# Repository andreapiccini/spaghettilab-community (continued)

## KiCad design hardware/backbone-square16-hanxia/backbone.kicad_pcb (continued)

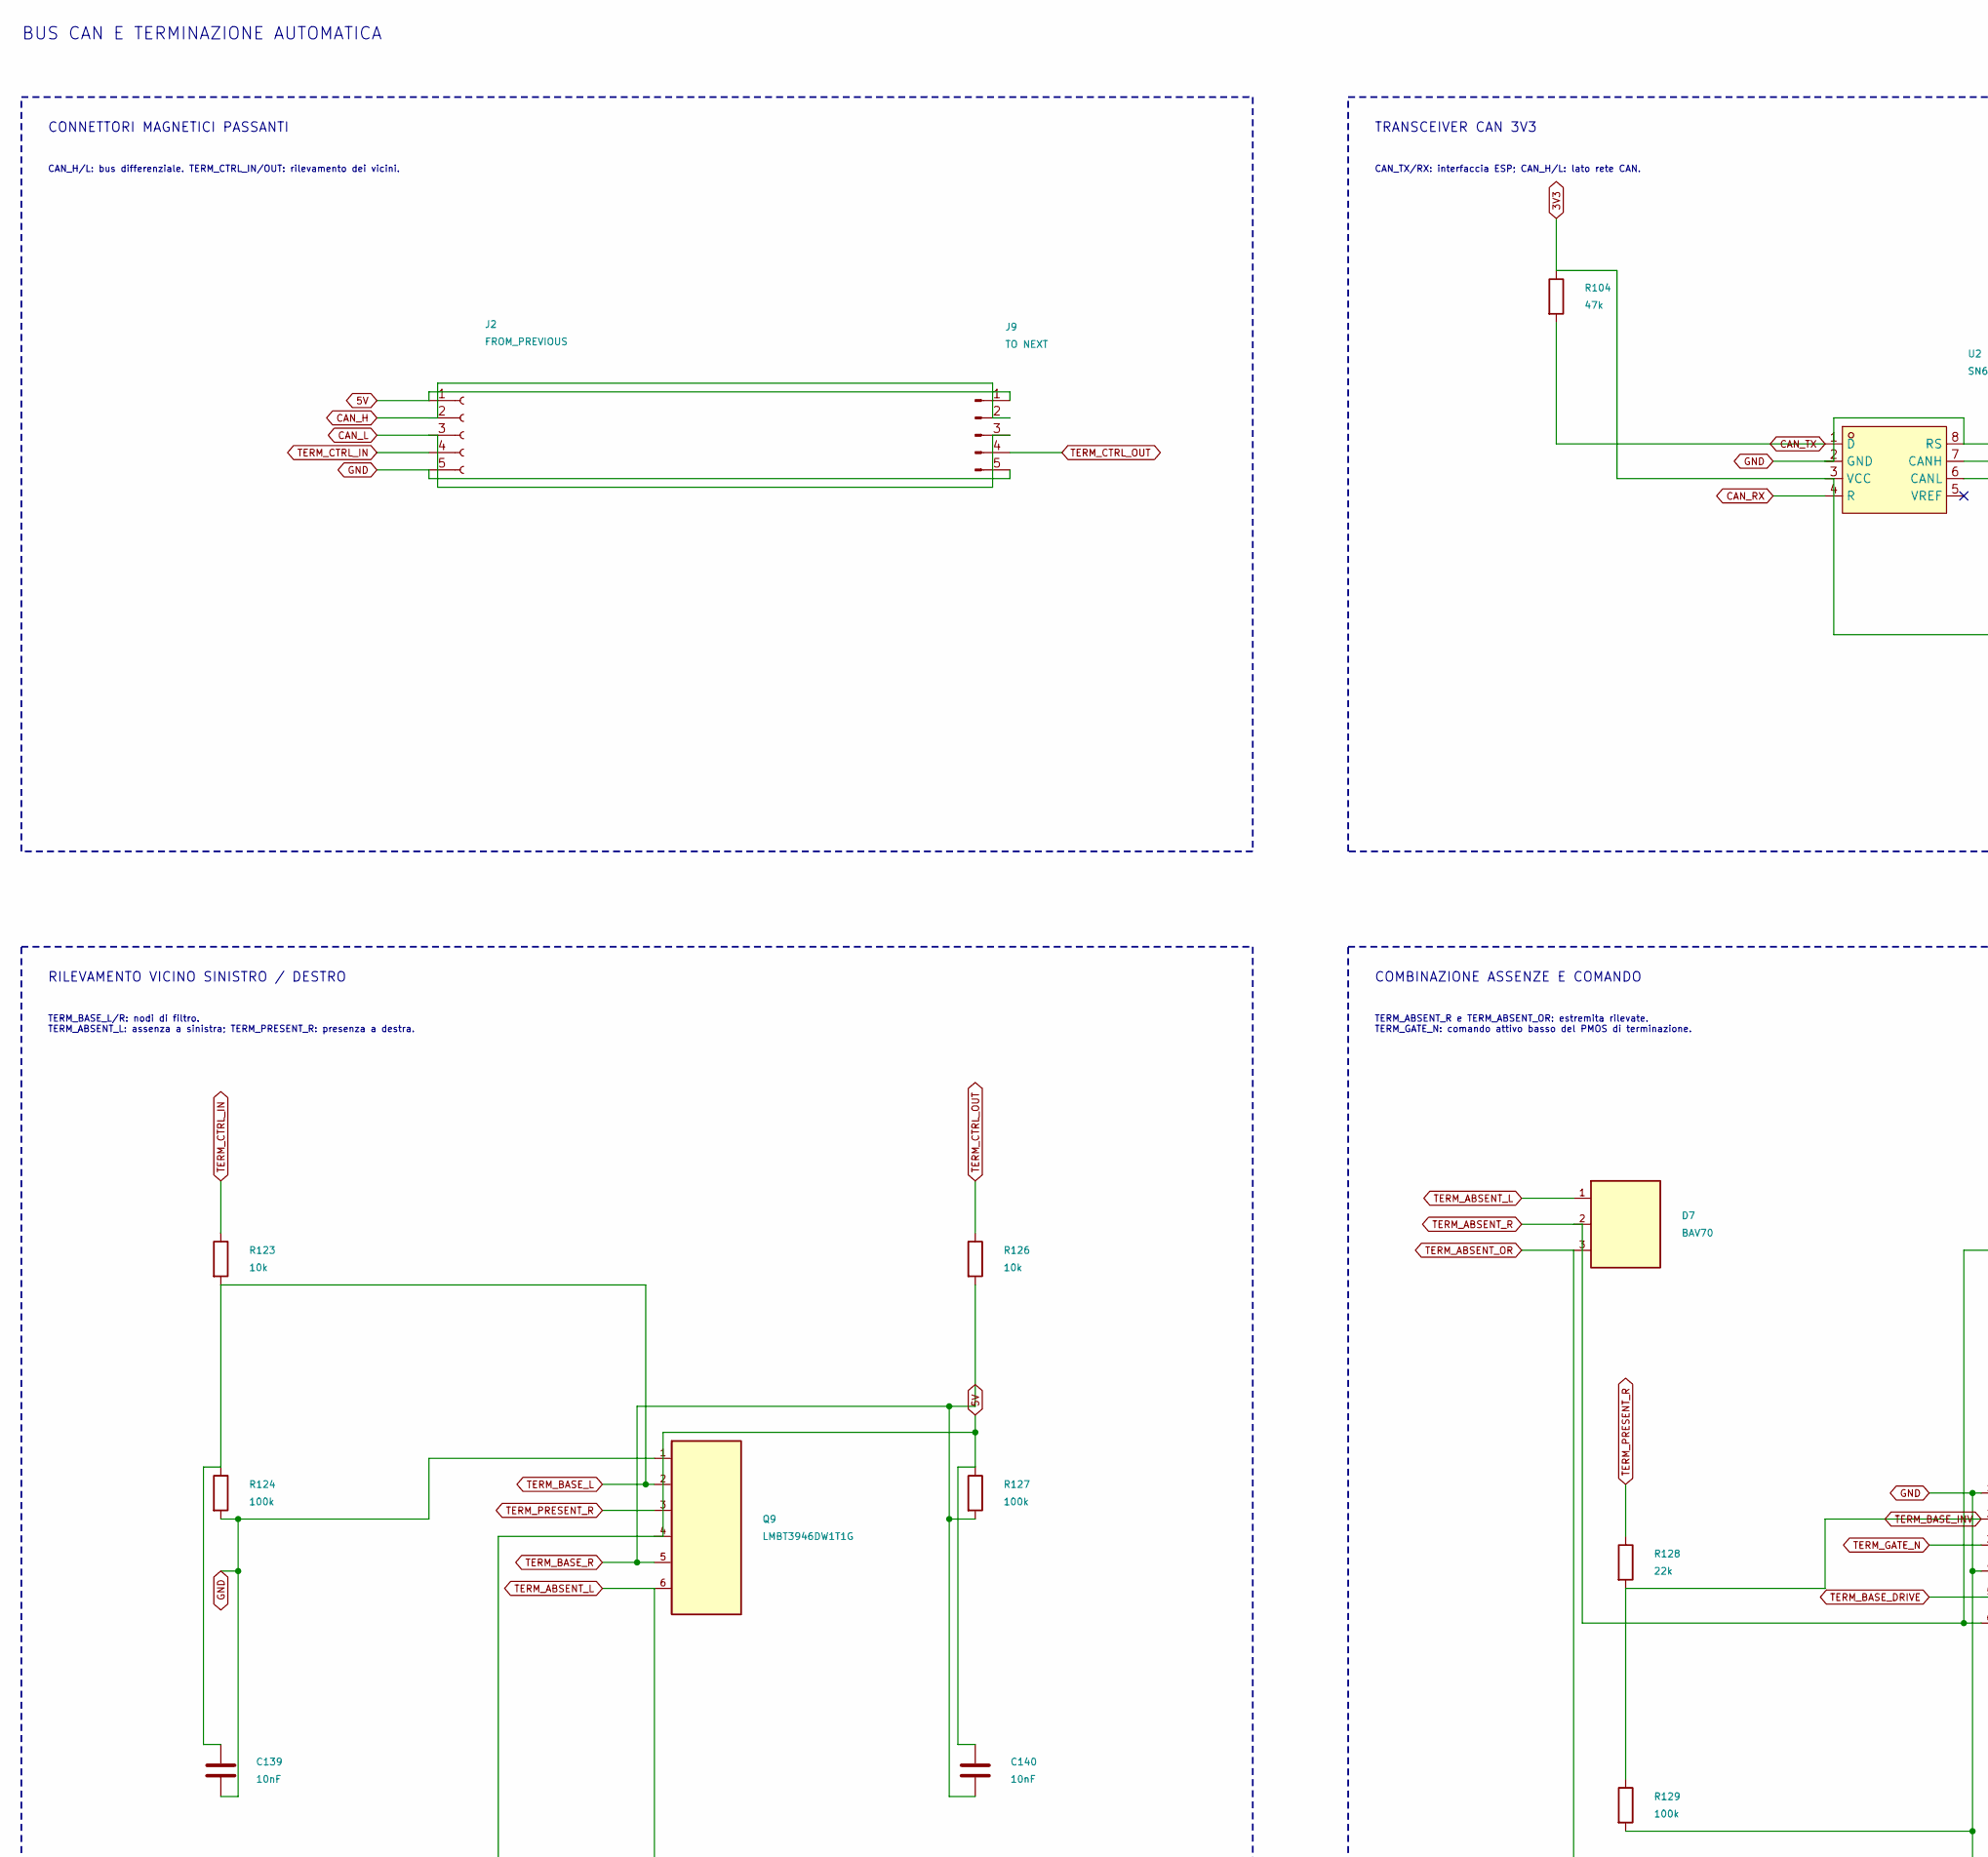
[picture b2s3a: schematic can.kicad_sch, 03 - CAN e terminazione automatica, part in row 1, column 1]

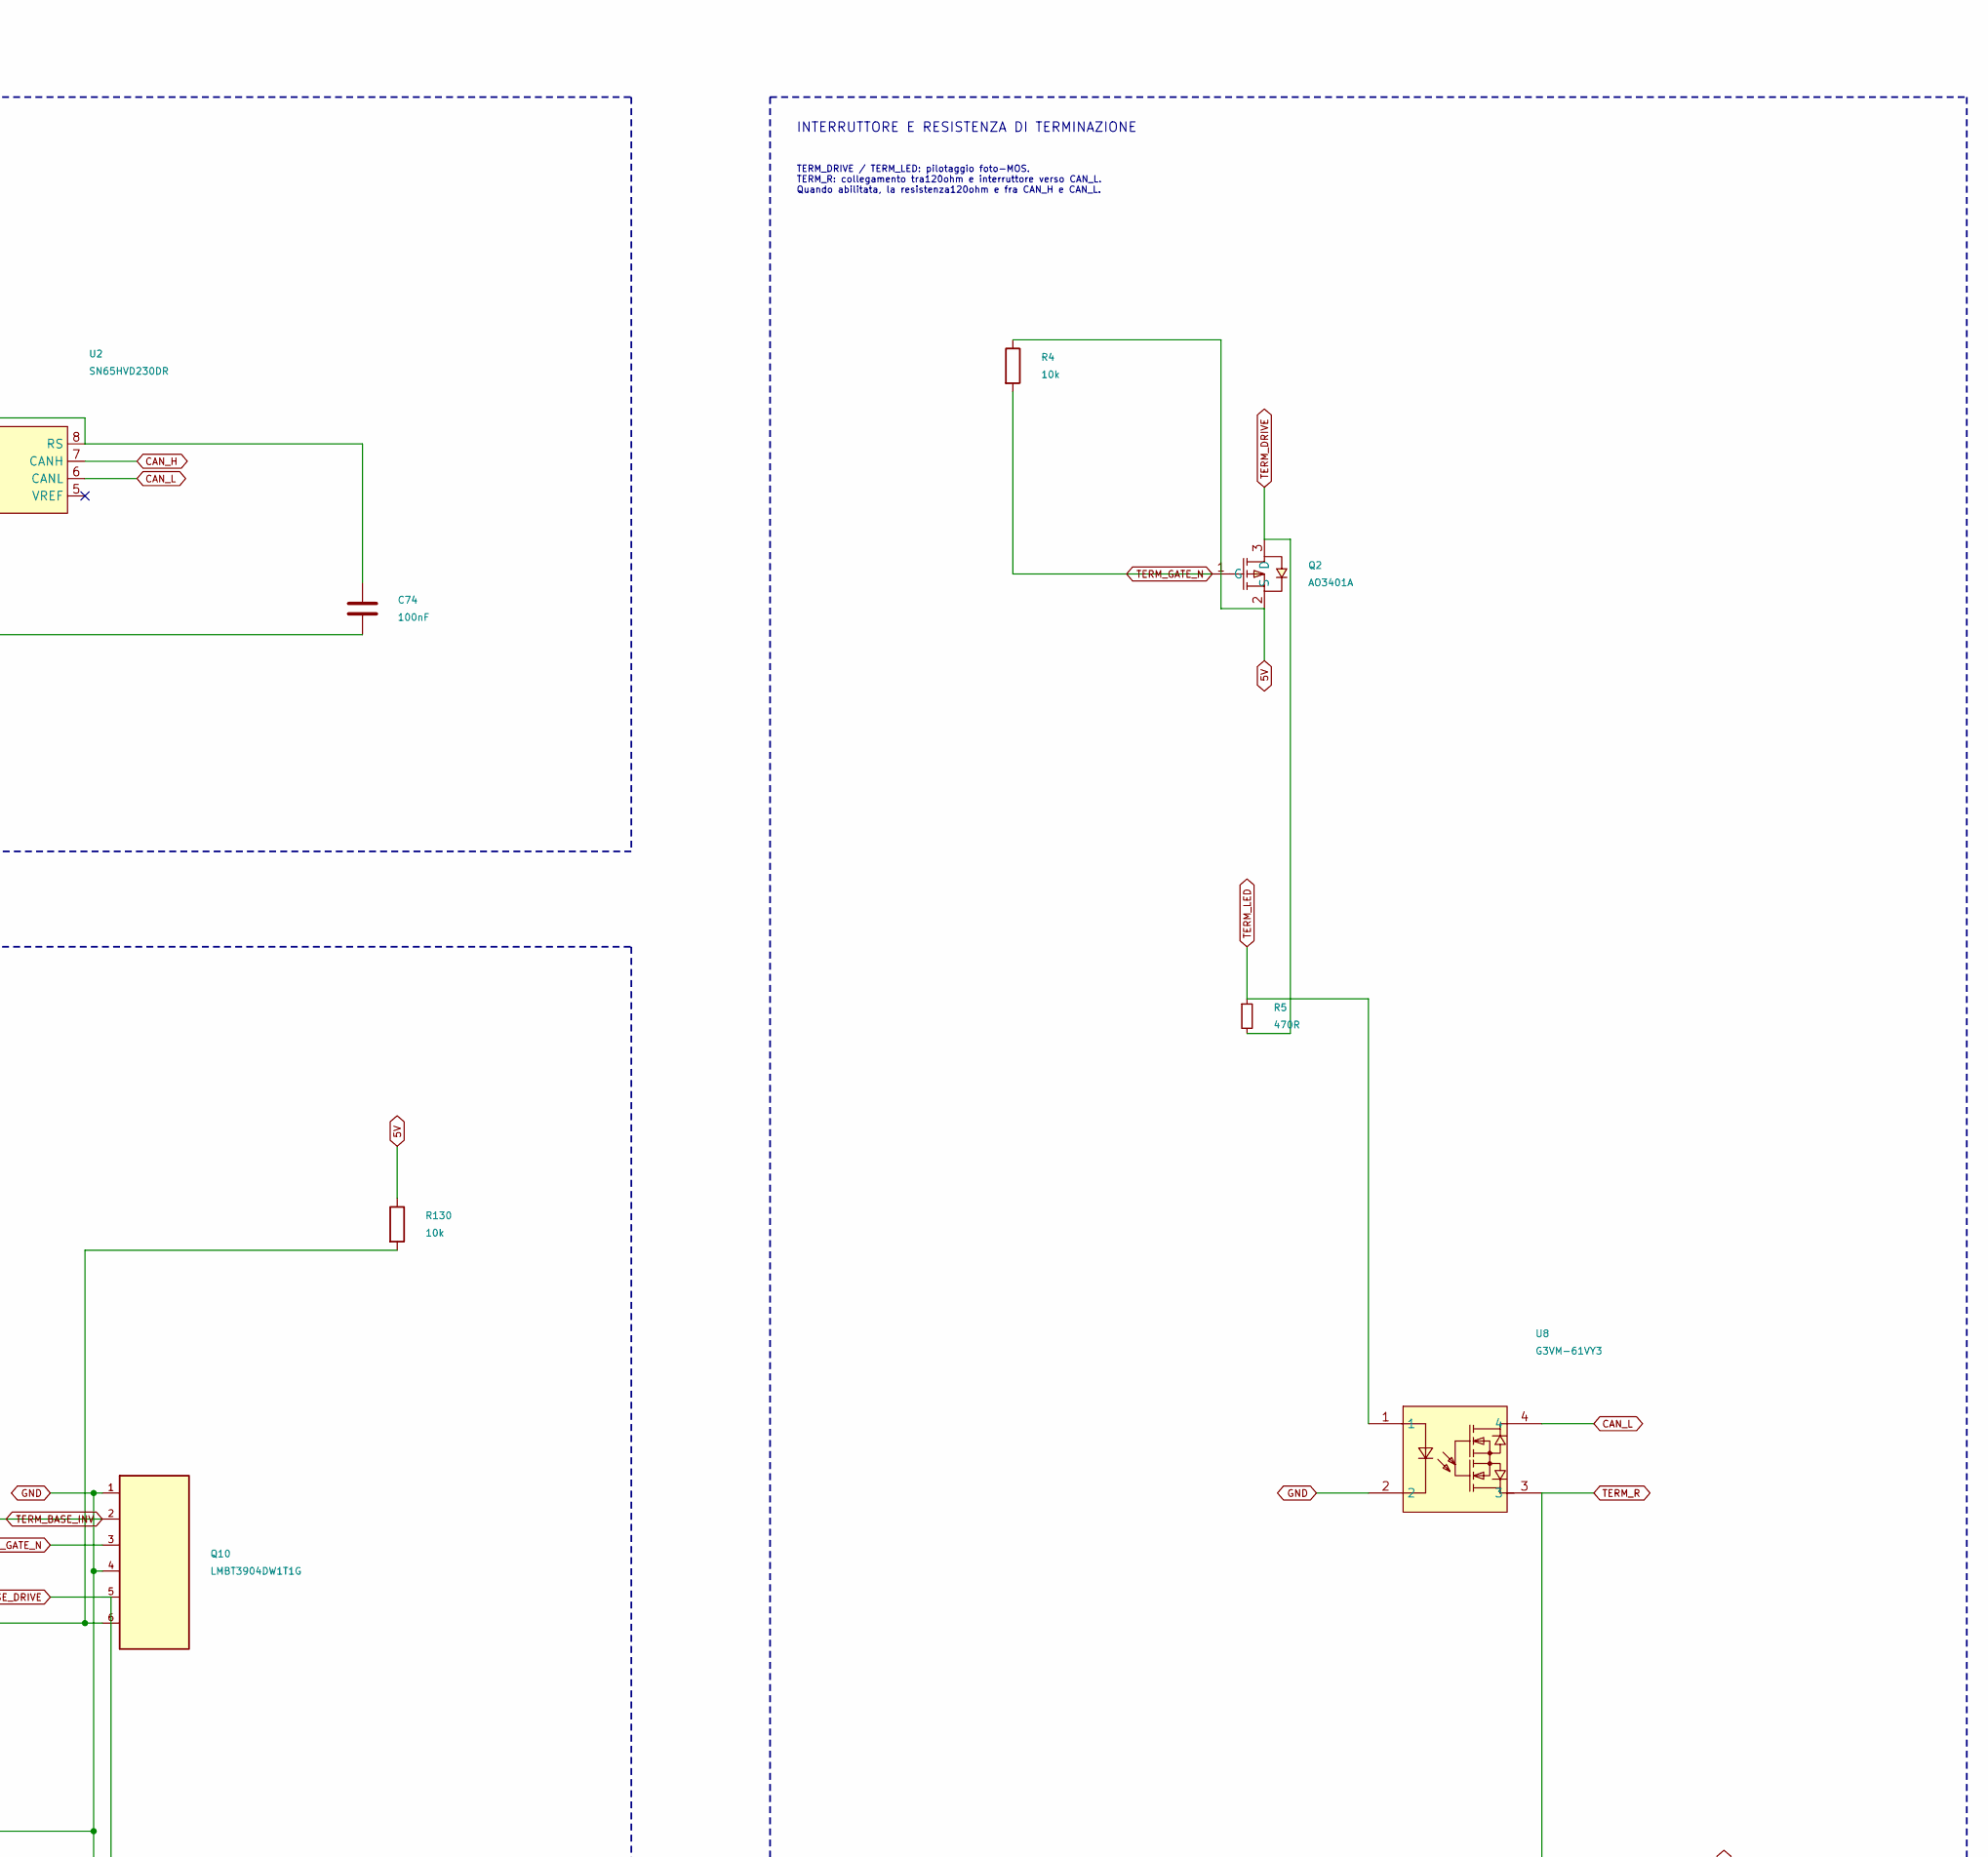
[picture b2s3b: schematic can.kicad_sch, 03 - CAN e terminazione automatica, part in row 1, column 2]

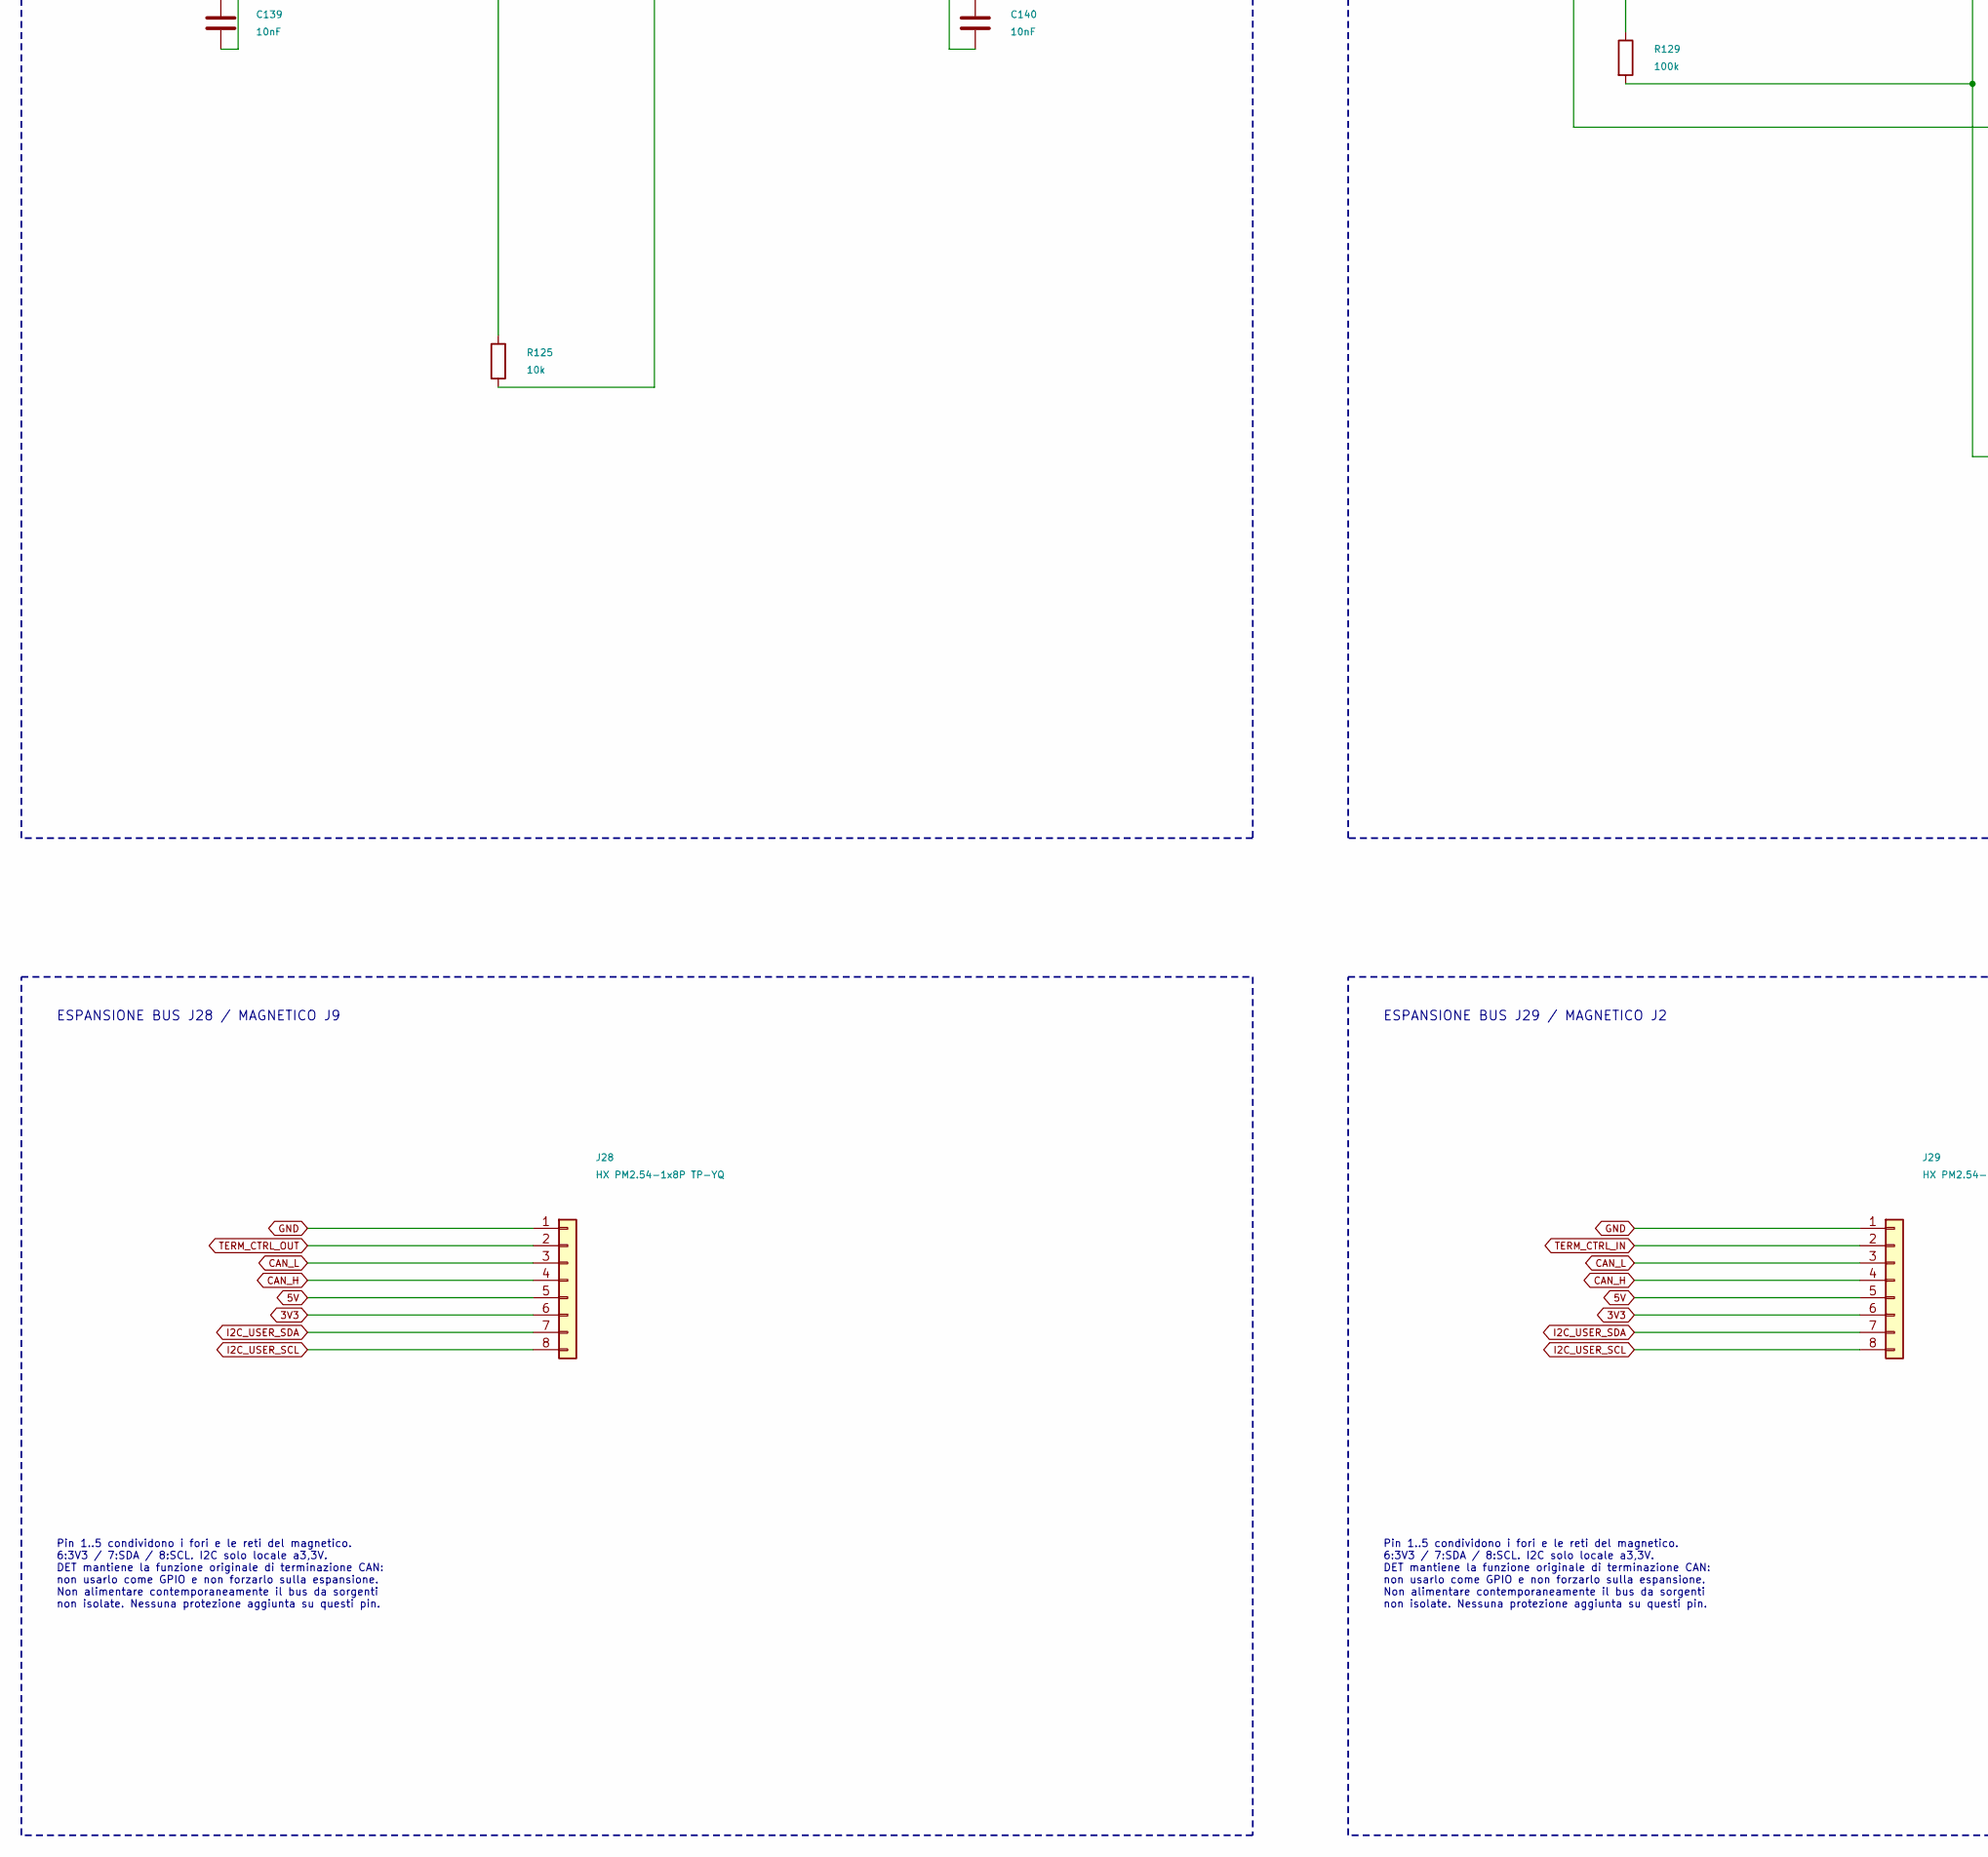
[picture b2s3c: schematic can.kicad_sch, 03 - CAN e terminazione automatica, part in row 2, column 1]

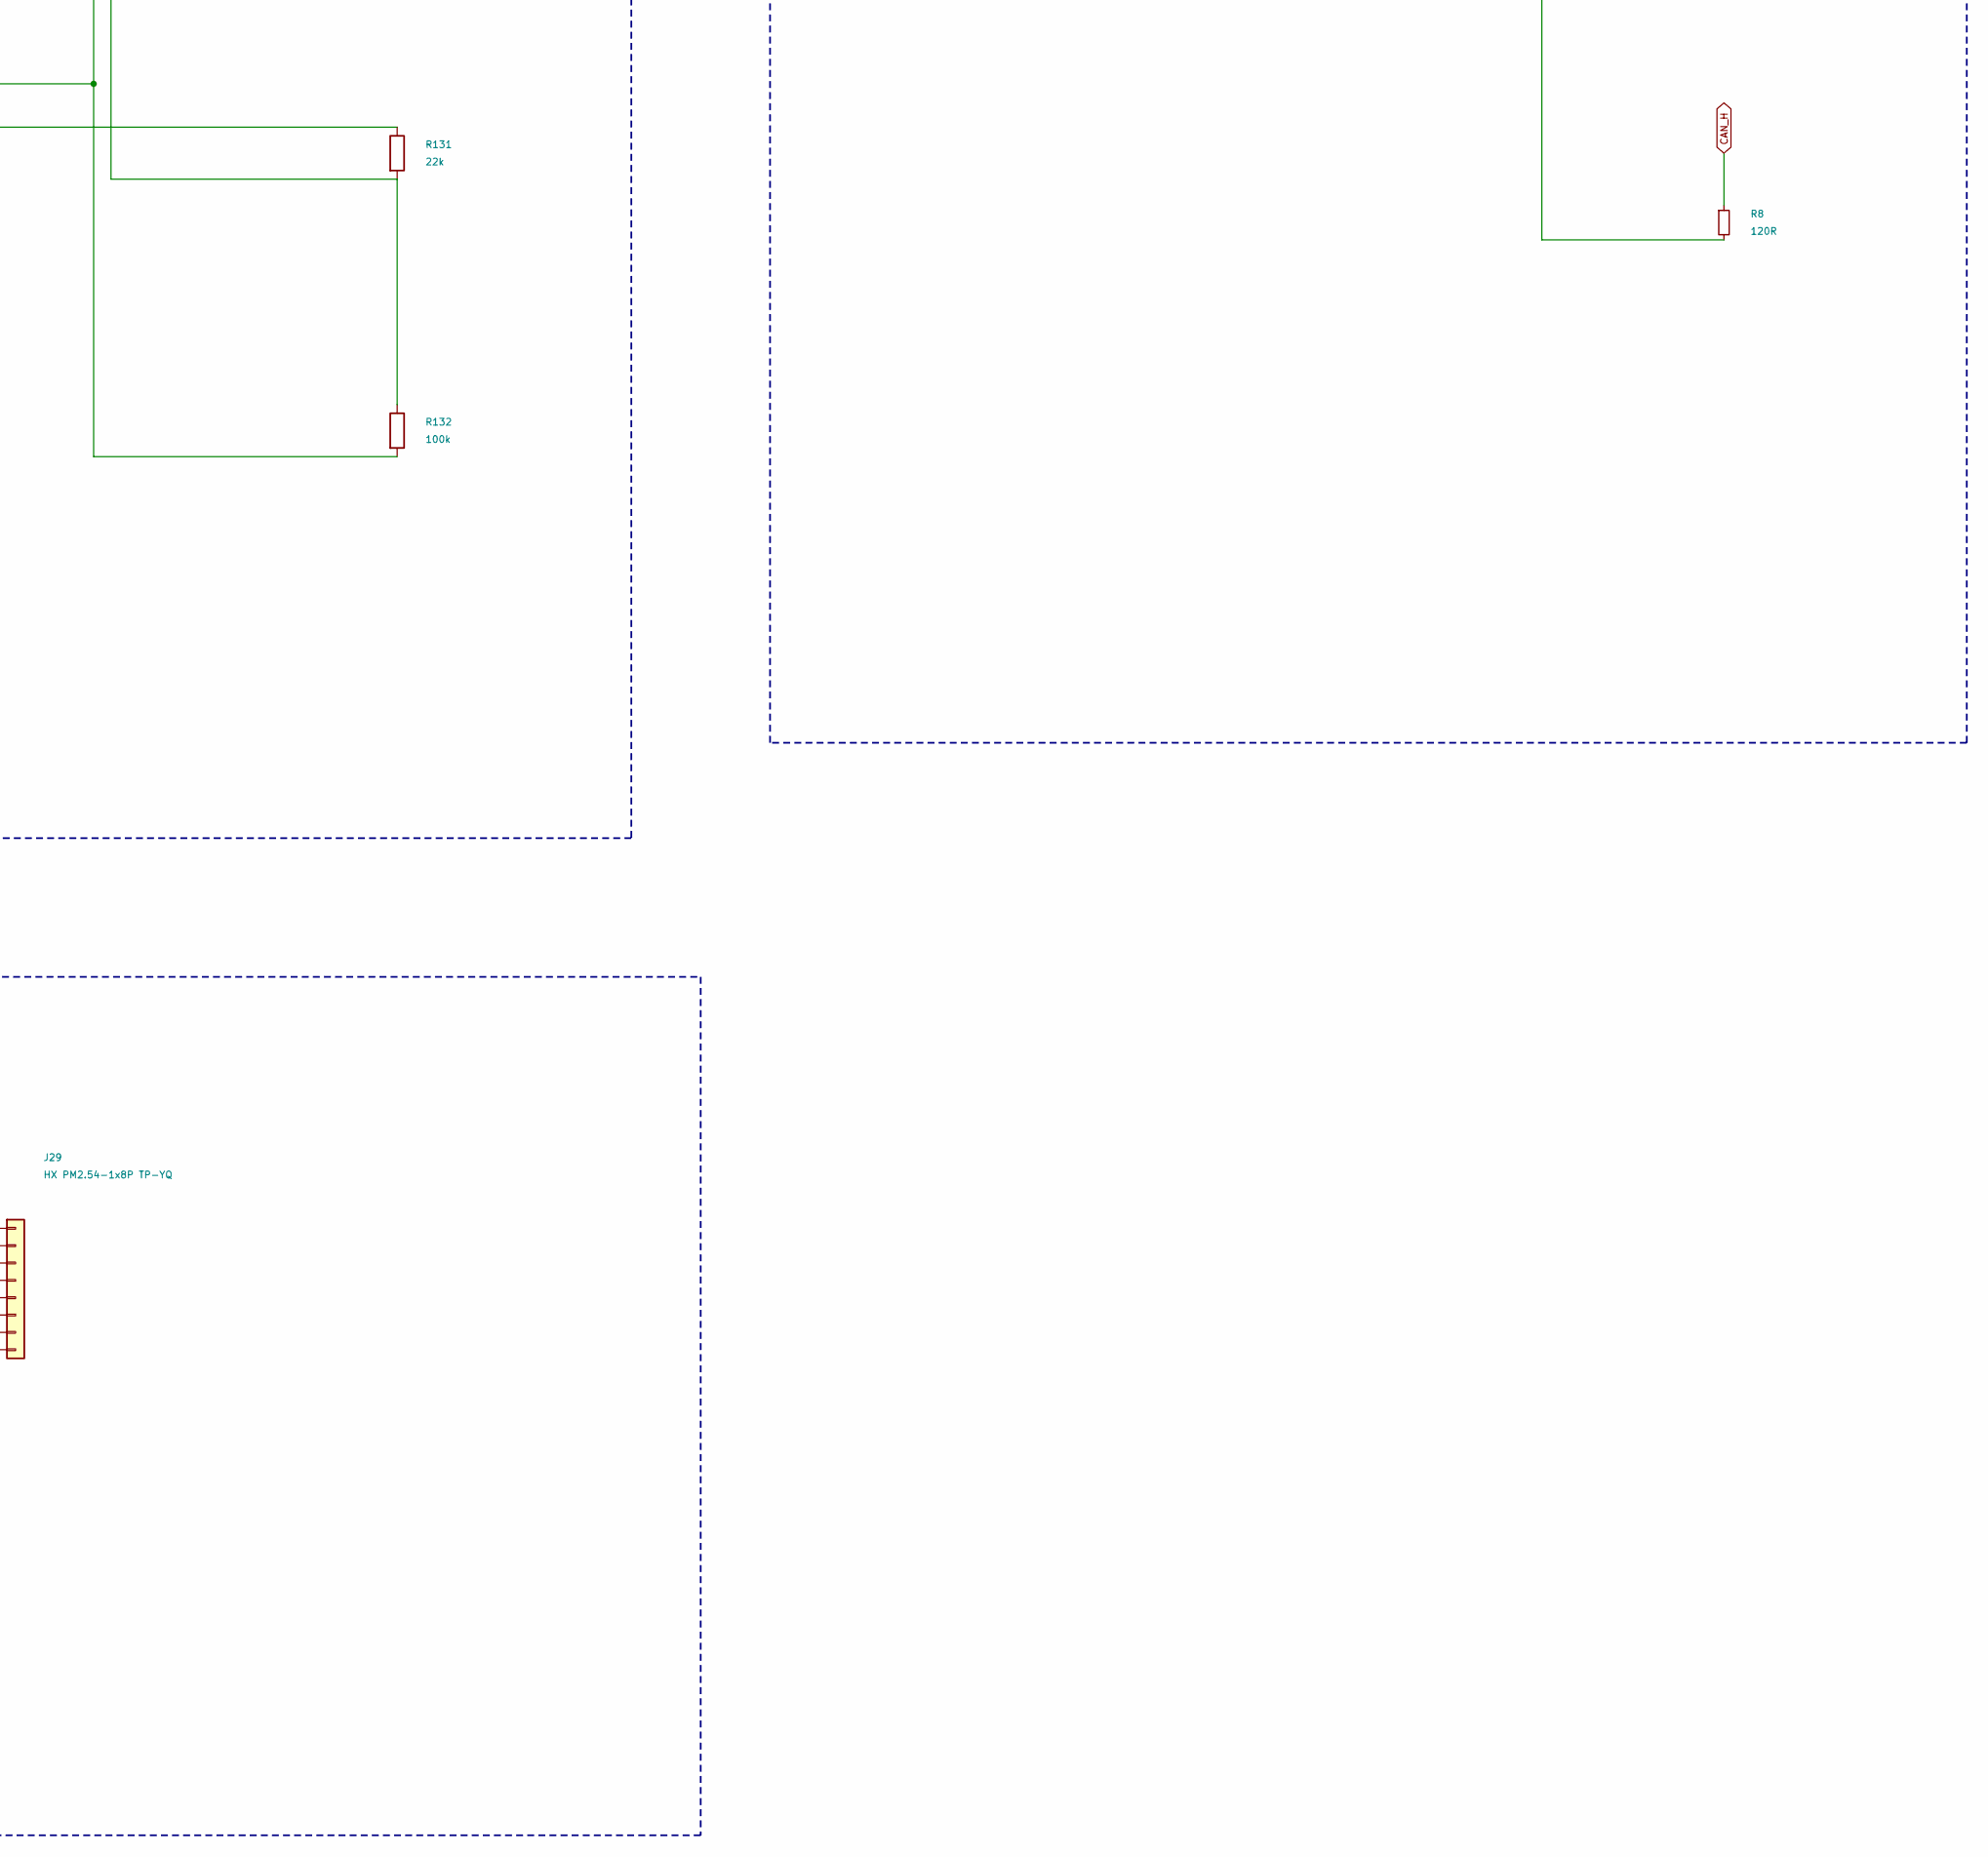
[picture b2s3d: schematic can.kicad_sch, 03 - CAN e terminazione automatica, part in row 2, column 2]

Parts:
C74: 100nF; C_0603_1608Metric
C139, C140: 10nF; C_0603_1608Metric; MPN CL10B103KB8NNNC; LCSC C1589
D7: BAV70; SOT-23; MPN BAV70; LCSC C68978
J2: FROM_PREVIOUS; Magnetic_J2_PTH_Module
J9: TO NEXT; Magnetic_J9_PTH_Module
J28, J29: HX PM2.54-1x8P TP-YQ; Hanxia_C42380985_1x08_MagneticSharedHoles; MPN HX PM2.54-1x8P TP-YQ; LCSC Part C42380985
Q2: AO3401A; SOT-23_L2.9-W1.3-P1.90-LS2.4-BR; MPN AO3401A; LCSC Part C15127
Q9: LMBT3946DW1T1G; SOT-363_SC-70-6; MPN LMBT3946DW1T1G; LCSC C136169
Q10: LMBT3904DW1T1G; SOT-363_SC-70-6; MPN LMBT3904DW1T1G; LCSC C131781
R4: 10k; R_0603_1608Metric
R5: 470R; R0603; MPN 0603WAF4700T5E; LCSC Part Name C23179
R8: 120R; R0603; MPN 0603WAF1200T5E; LCSC Part Name C2906988
R104: 47k; R_0603_1608Metric; MPN 0603WAF4702T5E; LCSC C25819
R123, R125, R126, R130: 10k; R_0603_1608Metric; MPN 0603WAF1002T5E; LCSC C25804
R124, R127, R129, R132: 100k; R_0603_1608Metric; MPN 0603WAF1003T5E; LCSC C25803
R128, R131: 22k; R_0603_1608Metric; MPN 0603WAF2202T5E; LCSC C31850
U2: SN65HVD230DR; SOIC-8_L4.9-W3.9-P1.27-LS6.0-BL; MPN SN65HVD230DR; LCSC Part C12084
U8: G3VM-61VY3; SMD-4_L4.6-W3.7-P2.54-LS7.0-TL; MPN G3VM-61VY3(TR); LCSC Part C2152318

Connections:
3V3: C74.2, J28.6, J29.6, R104.1, U2.3 (VCC); also elsewhere on the board
5V: C140.1, J2.1, J9.1, J28.5, J29.5, Q2.2 (S), Q9.4 (E), R4.1, R125.1, R127.1, R130.1; also elsewhere on the board
CAN_H: J2.2, J9.2, J28.4, J29.4, R8.1, U2.7 (CANH)
CAN_L: J2.3, J9.3, J28.3, J29.3, U2.6 (CANL), U8.4
CAN_RX: U2.4 (R); also elsewhere on the board
CAN_TX: R104.2, U2.1 (D); also elsewhere on the board
GND: C74.1, C139.2, J2.5, J9.5, J28.1, J29.1, Q9.1 (E), Q10.1 (E), Q10.4 (E), R124.2, R129.2, R132.2, U2.2 (GND), U2.8 (RS), U8.2; also elsewhere on the board
I2C_USER_SCL: J28.8, J29.8; also elsewhere on the board
I2C_USER_SDA: J28.7, J29.7; also elsewhere on the board
TERM_ABSENT_L: D7.1 (A), Q9.6 (C), R125.2
TERM_ABSENT_OR: D7.3 (K), R131.1
TERM_ABSENT_R: D7.2 (A), Q10.6 (C), R130.2
TERM_BASE_DRIVE: Q10.5 (B), R131.2, R132.1
TERM_BASE_INV: Q10.2 (B), R128.2, R129.1
TERM_BASE_L: C139.1, Q9.2 (B), R123.2, R124.1
TERM_BASE_R: C140.2, Q9.5 (B), R126.2, R127.2
TERM_CTRL_IN: J2.4, J29.2, R123.1
TERM_CTRL_OUT: J9.4, J28.2, R126.1
TERM_DRIVE: Q2.3 (D), R5.2; also elsewhere on the board
TERM_GATE_N: Q2.1 (G), Q10.3 (C), R4.2
TERM_LED: R5.1, U8.1
TERM_PRESENT_R: Q9.3 (C), R128.1
TERM_R: R8.2, U8.3

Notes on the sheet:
BUS CAN E TERMINAZIONE AUTOMATICA
CONNETTORI MAGNETICI PASSANTI
CAN_H/L: bus differenziale. TERM_CTRL_IN/OUT: rilevamento dei vicini.
TRANSCEIVER CAN 3V3
CAN_TX/RX: interfaccia ESP; CAN_H/L: lato rete CAN.
RILEVAMENTO VICINO SINISTRO / DESTRO
TERM_BASE_L/R: nodi di filtro. TERM_ABSENT_L: assenza a sinistra; TERM_PRESENT_R: presenza a destra.
COMBINAZIONE ASSENZE E COMANDO
TERM_ABSENT_R e TERM_ABSENT_OR: estremita rilevate. TERM_GATE_N: comando attivo basso del PMOS di terminazione.
INTERRUTTORE E RESISTENZA DI TERMINAZIONE
TERM_DRIVE / TERM_LED: pilotaggio foto-MOS. TERM_R: collegamento tra120ohm e interruttore verso CAN_L. Quando abilitata, la resistenza120ohm e fra CAN_H e CAN_L.
ESPANSIONE BUS J28 / MAGNETICO J9
Pin 1..5 condividono i fori e le reti del magnetico. 6:3V3 / 7:SDA / 8:SCL. I2C solo locale a3,3V. DET mantiene la funzione originale di terminazione CAN: non usarlo come GPIO e non forzarlo sulla espansione. Non alimentare contemporaneamente il bus da sorgenti non isolate. Nessuna protezione aggiu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
ESPANSIONE BUS J29 / MAGNETICO J2

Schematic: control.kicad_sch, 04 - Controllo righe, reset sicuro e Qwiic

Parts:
C200, C204, C205, C206: 100nF; C_0603_1608Metric
J4: SM04B-SRSS-TB(LF)(SN); JST_SH_SM04B-SRSS-TB_1x04-1MP_P1.00mm_Horizontal; MPN SM04B-SRSS-TB(LF)(SN); LCSC C160404
R24, R25: 4.7k; R0603
R203: 10k; R_0603_1608Metric
R302, R303: 4.7k; R_0603_1608Metric; MPN 0603WAF4701T5E; LCSC Part C23162
U40, U41, U42: FCA9539Q; FCA9539Q_WQFN24_4x4; MPN FCA9539Q; LCSC Part C55318342
U60: SN74LVC1G97DBVR; SOT-23-6; MPN SN74LVC1G97DBVR; LCSC Part C128411

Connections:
3V3: C200.1, C204.1, C205.1, C206.1, J4.2 (+3V3), R24.1, R25.1, R302.1, R303.1, U40.18 (A0), U40.21 (VCC), U41.21 (VCC), U41.23 (A1), U42.18 (A0), U42.21 (VCC), U42.23 (A1), U60.5 (VCC); also elsewhere on the board
ESP_EN: U60.1 (IN1 / EN); also elsewhere on the board
EXP_RESET_N: R203.1, U40.24 (RESET_N), U41.24 (RESET_N), U42.24 (RESET_N), U60.4 (Y); also elsewhere on the board
GND: C200.2, C204.2, C205.2, C206.2, J4.1 (GND), R203.2, U40.9 (GND), U40.23 (A1), U40.25 (EP / GND), U41.9 (GND), U41.18 (A0), U41.25 (EP / GND), U42.9 (GND), U42.25 (EP / GND), U60.2 (GND), U60.3 (IN0 = 0); also elsewhere on the board
I2C_INT_SCL: R303.2, U40.19 (SCL), U41.19 (SCL), U42.19 (SCL); also elsewhere on the board
I2C_INT_SDA: R302.2, U40.20 (SDA), U41.20 (SDA), U42.20 (SDA); also elsewhere on the board
I2C_USER_SCL: J4.4 (SCL), R25.2; also elsewhere on the board
I2C_USER_SDA: J4.3 (SDA), R24.2; also elsewhere on the board
ROW_ARM_N: U60.6 (IN2 / ARM_N); also elsewhere on the board
ROW_L01_ISO_N: U42.1 (P0.0); also elsewhere on the board
ROW_L01_NG: U40.2 (P0.1); also elsewhere on the board
ROW_L01_PG: U40.1 (P0.0); also elsewhere on the board
ROW_L02_ISO_N: U42.2 (P0.1); also elsewhere on the board
ROW_L02_NG: U40.4 (P0.3); also elsewhere on the board
ROW_L02_PG: U40.3 (P0.2); also elsewhere on the board
ROW_L03_ISO_N: U42.3 (P0.2); also elsewhere on the board
ROW_L03_NG: U40.6 (P0.5); also elsewhere on the board
ROW_L03_PG: U40.5 (P0.4); also elsewhere on the board
ROW_L04_ISO_N: U42.4 (P0.3); also elsewhere on the board
ROW_L04_NG: U40.8 (P0.7); also elsewhere on the board
ROW_L04_PG: U40.7 (P0.6); also elsewhere on the board
ROW_L05_ISO_N: U42.5 (P0.4); also elsewhere on the board
ROW_L05_NG: U40.11 (P1.1); also elsewhere on the board
ROW_L05_PG: U40.10 (P1.0); also elsewhere on the board
ROW_L06_ISO_N: U42.6 (P0.5); also elsewhere on the board
ROW_L06_NG: U40.13 (P1.3); also elsewhere on the board
ROW_L06_PG: U40.12 (P1.2); also elsewhere on the board
ROW_L07_ISO_N: U42.7 (P0.6); also elsewhere on the board
ROW_L07_NG: U40.15 (P1.5); also elsewhere on the board
ROW_L07_PG: U40.14 (P1.4); also elsewhere on the board
ROW_L08_ISO_N: U42.8 (P0.7); also elsewhere on the board
ROW_L08_NG: U40.17 (P1.7); also elsewhere on the board
ROW_L08_PG: U40.16 (P1.6); also elsewhere on the board
ROW_R01_ISO_N: U42.10 (P1.0); also elsewhere on the board
ROW_R01_NG: U41.2 (P0.1); also elsewhere on the board
ROW_R01_PG: U41.1 (P0.0); also elsewhere on the board
ROW_R02_ISO_N: U42.11 (P1.1); also elsewhere on the board
ROW_R02_NG: U41.4 (P0.3); also elsewhere on the board
ROW_R02_PG: U41.3 (P0.2); also elsewhere on the board
ROW_R03_ISO_N: U42.12 (P1.2); also elsewhere on the board
ROW_R03_NG: U41.6 (P0.5); also elsewhere on the board
ROW_R03_PG: U41.5 (P0.4); also elsewhere on the board
ROW_R04_ISO_N: U42.13 (P1.3); also elsewhere on the board
ROW_R04_NG: U41.8 (P0.7); also elsewhere on the board
ROW_R04_PG: U41.7 (P0.6); also elsewhere on the board
ROW_R05_ISO_N: U42.14 (P1.4); also elsewhere on the board
ROW_R05_NG: U41.11 (P1.1); also elsewhere on the board
ROW_R05_PG: U41.10 (P1.0); also elsewhere on the board
ROW_R06_ISO_N: U42.15 (P1.5); also elsewhere on the board
ROW_R06_NG: U41.13 (P1.3); also elsewhere on the board
ROW_R06_PG: U41.12 (P1.2); also elsewhere on the board
ROW_R07_ISO_N: U42.16 (P1.6); also elsewhere on the board
ROW_R07_NG: U41.15 (P1.5); also elsewhere on the board
ROW_R07_PG: U41.14 (P1.4); also elsewhere on the board
ROW_R08_ISO_N: U42.17 (P1.7); also elsewhere on the board
ROW_R08_NG: U41.17 (P1.7); also elsewhere on the board
ROW_R08_PG: U41.16 (P1.6); also elsewhere on the board

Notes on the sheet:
CONTROLLO48SEGNALI / RESET SICURO / I2C
U40 | FCA9539Q | 0x75
PG/NG banco A: comandi di alimentazione. SCL/SDA: I2C; A0/A1: indirizzo; INT_N non usato.
U41 | FCA9539Q | 0x76
PG/NG banco B: comandi di alimentazione. SCL/SDA: I2C; A0/A1: indirizzo; INT_N non usato.
U42 | FCA9539Q | 0x77
ISO_N A/B: isolamento GPIO, attivo basso. SCL/SDA: I2C; A0/A1: indirizzo; INT_N non usato.
BUS UTENTE GPIO11/12 / QWIIC / PULL-UP
I2C_USER indipendente dai3expander: SDA GPIO11 / SCL GPIO12. Pull-up4,7k a3V3. 3V3/GND: alimentazione del moduloQwiic.
INTERBLOCCO RESET / UNA SOLA PORTA
EXP_RESET_N = ESP_EN AND NOT ROW_ARM_N. IN0 aGND. R203 mantiene reset basso se non pilotato; C200 bypass100nF.
BUS INTERNO DEDICATO / GPIO4 SDA / GPIO5 SCL
R302/R303: pull-up4,7k del solo bus interno. R24/R25: pull-up4,7k del bus utente, nel blocco Qwiic. Nessun collegamento SDA/SCL tra i due bus. Entrambi usano livelli3,3V; firmware: due controller distinti.
INTERFACCIA LOCALE | DUE PULSANTI XKB
